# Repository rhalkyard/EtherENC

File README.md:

# ENC624J600-based Ethernet card for Acorn Archimedes and Risc PC systems

From the same person who still hasn't quite finished
[SEthernet](https://github.com/rhalkyard/SEthernet), comes yet another Ethernet
card for vintage computers!

Ethernet cards for Acorn systems are even harder to find than for vintage Macs.
This project is an attempt to bring a modern, low-cost Ethernet card to Acorn
Archimedes and Risc PC machines.

## Project Status

Early days yet! I have the driver functioning on a prototype version of the
card, but there are enough issues that it'll need a redone board before I'm
truly happy with it.

Meanwhile, someone else in the Acorn community who has access to a lot more
hardware for testing, has [announced his own open-source Ethernet
podule](https://www.stardot.org.uk/forums/viewtopic.php?p=468283). To be
brutally honest, his design is probably the sensible path forward, and there
probably isn't room for two very similar projects in such a small community, so
this project's future is in question. However, I'm proud of what I accomplished,
my design works well (in my opinion), and I think it's worth saving for
posterity, so here it is.

## Supported Systems

The intent is for this card to be compatible with any RISC OS machine with 16-
or 8-bit Podule slots, running RISC OS 3.10 or later. However, I only have
access to an A3000, so testing on later OSes and other machines will be up to
others!

## Hardware

See [HARDWARE.md](HARDWARE.md) for a design overview.

Schematic in PDF format can be found at
[pcb/EtherENC-prototype/EtherENC-Prototype.pdf](pcb/EtherENC-prototype/EtherENC-Prototype.pdf).

## Software

The [EtherENC/](EtherENC) directory contains driver source, buildable with Acorn
C/C++ version 5, which can be obtained from
[https://www.4corn.co.uk/articles/acornc5/](https://www.4corn.co.uk/articles/acornc5/),
or included in [RPCEMU](https://www.marutan.net/rpcemu/index.php)'s RISC OS 3.71
Easy-Start bundle.

If you are not used to RISC OS, the filenames and layout will look a little
weird. Instead of having extensions, `.c` and `.h` files live in separate
directories, and the comma-suffixes on various file names encode RISC OS file
types. Of particular interest, the `,ffb` files are BBC Basic programs, however
these are stored in a binary format and their source is not easily viewable on
non-RISC OS systems. Accompanying text dumps of the program code are included
alongside, I will endeavour to keep these up to date.

`MkROM` is a BASIC program that builds the card's ROM image with the appropriate
headers and loadable driver module.

`WriteROM` can then be used to program or update the card's flash with the new
ROM image.

### Checkout

Note that this repository includes the [RISC OS Open TCPIPLibs
source](https://gitlab.riscosopen.org/RiscOS/Sources/Lib/TCPIPLibs) as a
submodule. Specifically, it uses the
[TCPIPLibs-5_01](https://gitlab.riscosopen.org/RiscOS/Sources/Lib/TCPIPLibs/-/tree/TCPIPLibs-5_01)
tag, as this corresponds to the DCI 4.04 specification, without bringing in a
bunch of changes that make old versions of Acorn C/C++ get confused.

After cloning this repo, run `git submodule update --init` to set up submodules
correctly.

### Building

1. Install Acorn C/C++ and run `!SetPaths` inside the Acorn C/C++ directory.

2. Run the `!Mk` script in the source directory (or run `amu` from a TaskWindow
   or CLI).

### Flashing

1. After building the EtherENC driver, run `WriteROM` and follow the prompts.

### Installation

These instructions assume that you are using the version of `!Internet` included
in the Universal !Boot distribution. If you are using something else, you should
probably be able to figure out how to adapt them to your setup!

1. Copy `AutoSense.EtherENC` to
   `!Boot.Resources.Configure.!InetSetup.AutoSense`.

2. (optional) Copy the built `EtherENC` module to
   `!Boot.Resources.System.Modules.Network`. The driver module from the card ROM
   should be sufficient, but when testing it can be useful to softload the
   module instead.

3. Restart RISC OS.

### Configuring

Configuring the card is more or less the same as any other network interface on
RISC OS, and is done by the `!Boot.Resources.Configure.!InetSetup` application:

1. Run `!Boot.Resources.Configure.!InetSetup`, and click the `Internet` icon.

2. Under `Interfaces`, tick the box next to `EtherENC`, click the adjacent
   `Configure...` button, and set your IP address and netmask. Unless you know
   what you're doing, `Obtain IP address` should be set to `Manually`, and
   `Primary interface` should be ticked.

2. Under `Routing`, enter your default gateway. Unless you know what you're
   doing, `Act as an IP router` and `Run RouteD` should not be ticked.

3. Under `Host names`, ether your hostname domain, and DNS server(s). Ensure
   that `Use name servers also` is selected.

4. Configure AUN and Access if necessary (doing so is beyond the scope of this
   document).

#### CMOS Settings

The system's CMOS memory is used to store hardware configuration options across
reboots. These options can be set and read using RISC OS' `*Configure` and
`*Status` commands.

`*Configure EENCFlow <unit> Off|On` - Enable or disable PAUSE-frame flow
control, which may help mitigate packet drops on heavily-loaded systems. Default
is `Off`. Flow control can only operate on full-duplex links.

`*Configure EENCLink <unit> Auto | 10 Half|Full | 100 Half|Full` - Configure
link mode. `Auto` (the default) causes link speed and duplex mode to be
autonegotiated with the link partner. Otherwise, a fixed speed and duplex
setting (one of `10 Half`, `10 Full`, `100 Half` or `100 Full`) can be set.

After installing the card, or moving it into another slot, it may be necessary
to reconfigure the card in order to overwrite any leftover CMOS settings from
previous residents of that slot. Defaults can be restored with:

```
*Configure EENCLink <unit> Auto
*Configure EENCFlow <unit> Off
```

## Licenses

Hardware (everything in the `pcb` and `pld` directories) is licensed under the
CERN Open Hardware License Version 2 - Strongly Reciprocal.

The driver (everything in the `EtherENC` directory) is licensed under the GNU
Public License Version 3, with the following exceptions:

- `EtherENC.s.iocopy` contains code derived from the 
  ["Ether1" driver](https://gitlab.riscosopen.org/RiscOS/Sources/Networking/Ethernet/Ether1/) 
  as published by Risc OS Online Ltd., under the Apache License, version 2.0.

- `EtherENC.h.filter` and `EtherENC.c.filter` contain code derived from the
  ["EtherY" driver](https://gitlab.riscosopen.org/RiscOS/Sources/Networking/Ethernet/EtherY/)
  as published by RISC OS Online Ltd., under the BSD License.

- `EtherENC.h.syslog` and `EtherENC.s.syslog` are included unmodified from the
  SysLog freeware application (https://compton.nu/software/riscos/syslog).

## To Do

- Finalise hardware design

- Performance testing and driver optimisation

## Allocations

Names and IDs registered with ROOL (see
[https://www.riscosopen.org/content/allocate](https://www.riscosopen.org/content/allocate)
for info). If you fork EtherENC and make software-incompatible changes, please
request your own allocations, as these are registered to me personally. However,
if your EtherENC-derived hardware is fully compatible with the mainline EtherENC
driver, you are welcome to use the same Podule IDs.

| Allocation Type        | Allocation                                     | Source locations                                           |
| ---------------------- | ---------------------------------------------- | ---------------------------------------------------------- |
| Ethernet Driver Suffix | `ENC`                                          | Everywhere                                                 |
| SWI Base               | &5A9C0                                         | [`cmhg.ModuleHdr`](cmhg/ModuleHdr)                         |
| Module Name            | `EtherENC`                                     | [`cmhg.ModuleHdr`](cmhg/ModuleHdr)                         |
| Commands               | `EENCInfo`, `EENCTest`, `EENCFlow`, `EENCLink` | [`cmhg.ModuleHdr`](cmhg/ModuleHdr), [`c.module`](c/module) |
| Error Block            | &822800                                        | [`h.errors`](h/errors), [`MkROM`](MkROM.bas)               |
| Podule Manufacturer ID | &72                                            | [`h.if_enc`](h/if_enc), [`MkROM`](MkROM.bas)               |
| Podule Type ID         | &14E (16 bit), &14F (8 bit)                    | [`h.if_enc`](h/if_enc), [`MkROM`](MkROM.bas)               |

## References

- [RISC OS 3 Programmer's Reference Manual](http://www.riscos.com/support/developers/prm/)

- [Acorn Enhanced Expansion Card
  Specification](https://www.chiark.greenend.org.uk/~theom/riscos/docs/expspec.pdf)

- [RISC OS DCI4 Reference Manuals](https://gerph.github.io/riscos-prm-dci4/)

- [Ether1 (AMD LANCE-based card) driver source](https://gitlab.riscosopen.org/RiscOS/Sources/Networking/Ethernet/Ether1)

- [EtherY (LAN91C111-based card) driver source](https://gitlab.riscosopen.org/RiscOS/Sources/Networking/Ethernet/EtherY/)

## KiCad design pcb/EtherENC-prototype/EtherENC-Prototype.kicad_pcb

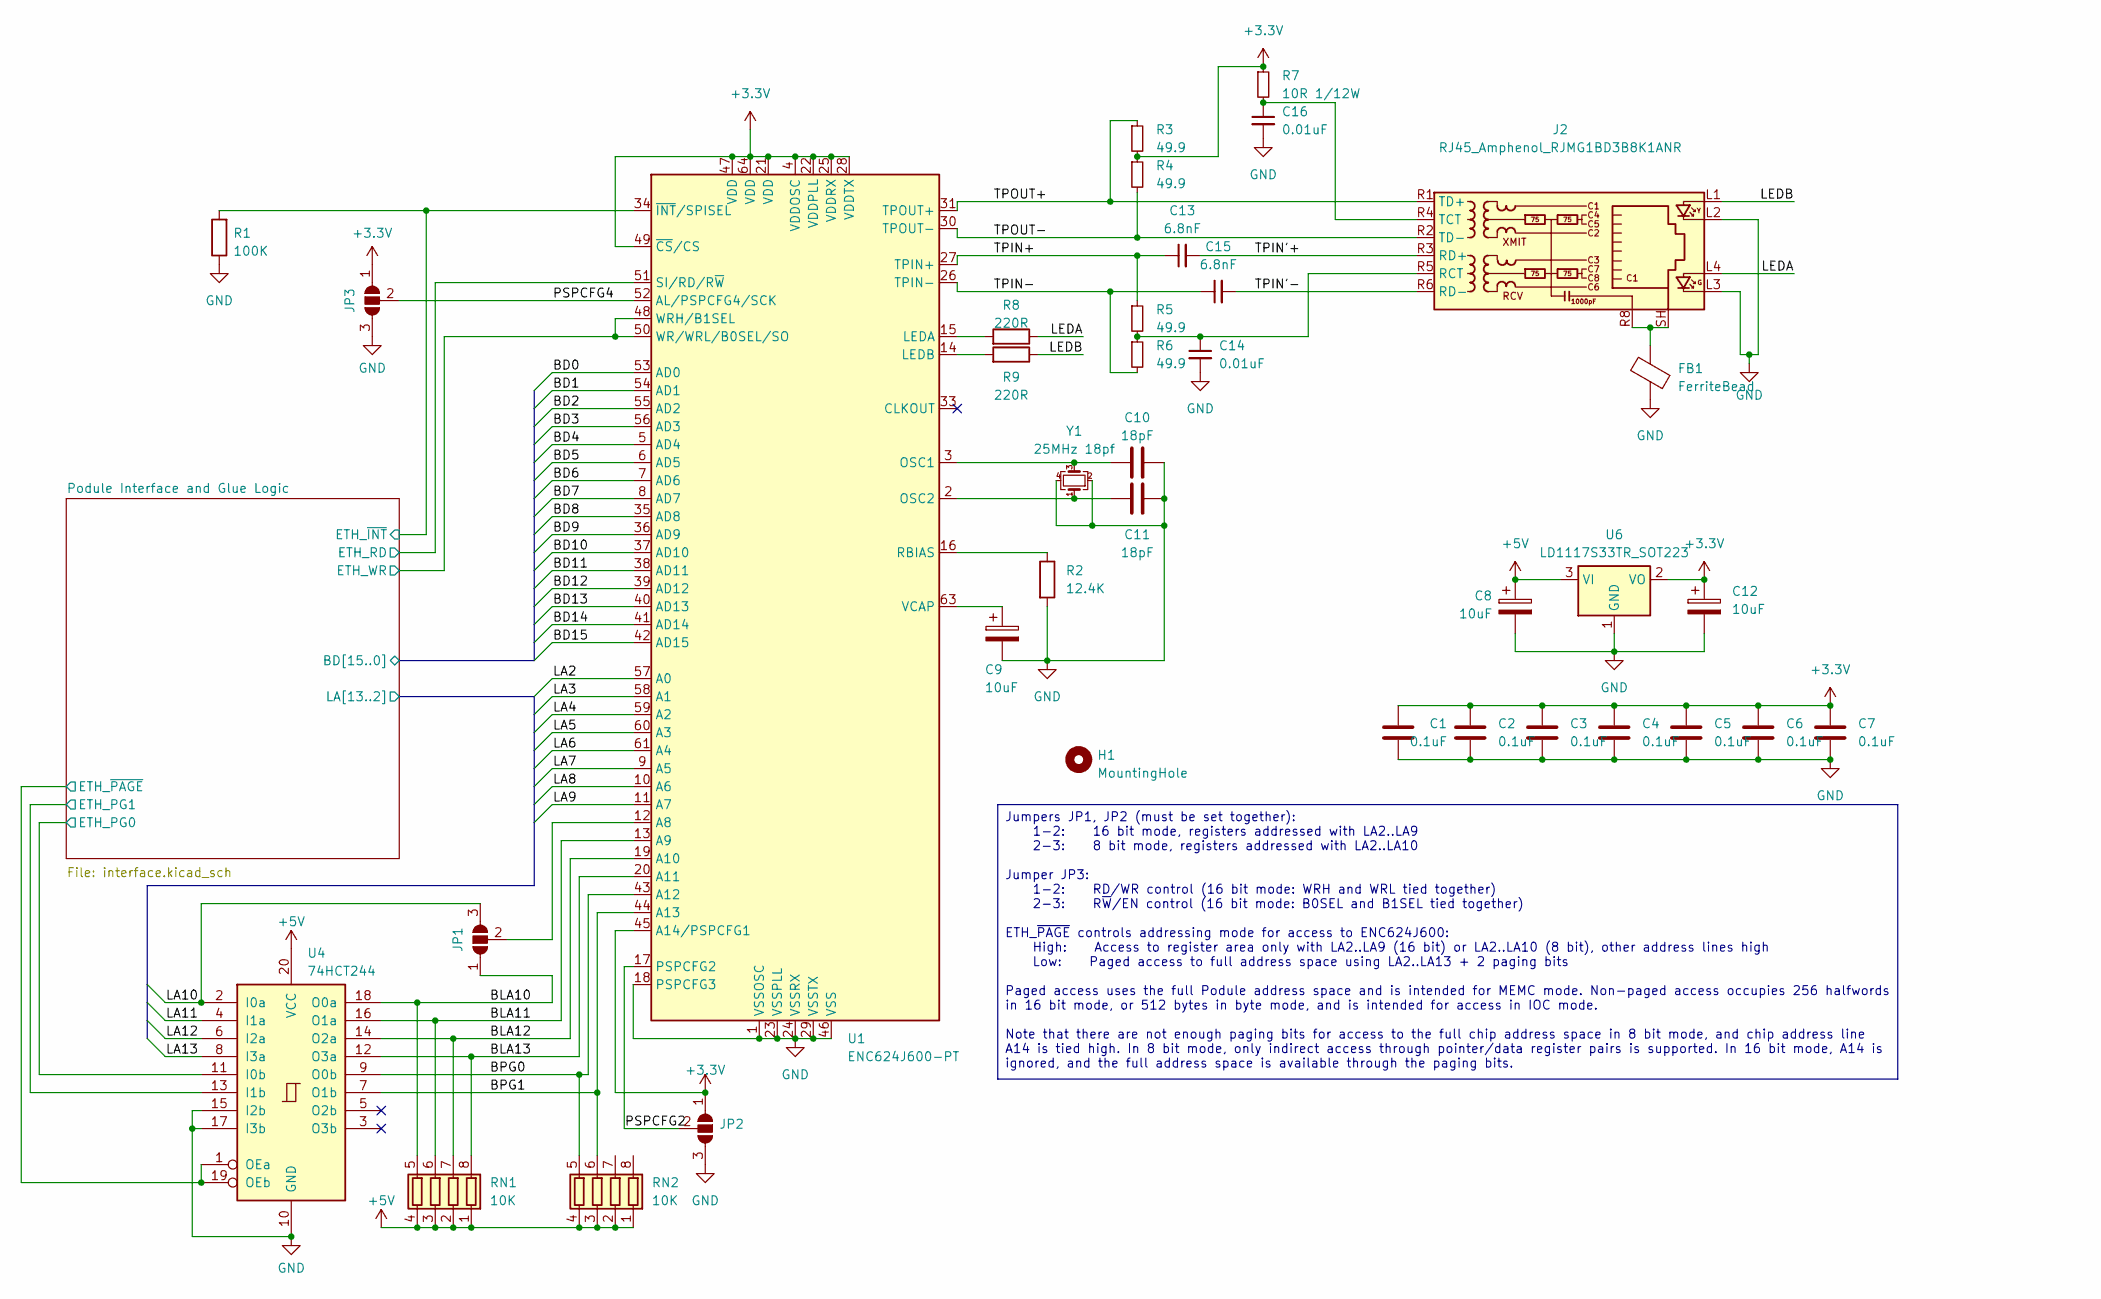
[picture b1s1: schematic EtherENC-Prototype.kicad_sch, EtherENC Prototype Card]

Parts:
C1, C2, C3, C4, C5, C6, C7: 0.1uF; C_0805_2012Metric_Pad1.18x1.45mm_HandSolder; Digikey 399-C0805C104M5RAC7800CT-ND
C8, C9, C12: 10uF; CP_EIA-3216-18_Kemet-A_Pad1.58x1.35mm_HandSolder; Digikey 718-1118-1-ND
C10, C11: 18pF; C_0805_2012Metric_Pad1.18x1.45mm_HandSolder; Digikey 399-C0805C180K5GAC7800CT-ND
C13, C15: 6.8nF; C_0805_2012Metric_Pad1.18x1.45mm_HandSolder; Digikey 399-C0805C682K5RAC7800CT-ND
C14, C16: 0.01uF; C_0805_2012Metric_Pad1.18x1.45mm_HandSolder; Digikey 399-C0805C103K5RACTUCT-ND
FB1: FerriteBead; L_0805_2012Metric_Pad1.15x1.40mm_HandSolder; Digikey 240-2549-1-ND
H1: MountingHole; MountingHole_3.2mm_M3
J2: RJ45_Amphenol_RJMG1BD3B8K1ANR; Digikey RJMG1BD3B8K1ANR-ND
JP1, JP2, JP3: SolderJumper_3_Open; SolderJumper-3_P1.3mm_Open_RoundedPad1.0x1.5mm
R1: 100K; R_0805_2012Metric_Pad1.20x1.40mm_HandSolder; Digikey RMCF0805FT100KCT-ND
R2: 12.4K; R_0805_2012Metric_Pad1.20x1.40mm_HandSolder; Digikey RMCF0805FT12K4CT-ND
R3, R4, R5, R6: 49.9; R_0805_2012Metric_Pad1.20x1.40mm_HandSolder; Digikey RMCF0805FT49R9CT-ND
R7: 10R 1/12W; R_0805_2012Metric_Pad1.20x1.40mm_HandSolder; Digikey RMCF0805FT10R0CT-ND
R8, R9: 220R; R_0805_2012Metric_Pad1.20x1.40mm_HandSolder; Digikey RMCF0805FT221RCT-ND
RN1, RN2: 10K; R_Array_Concave_4x0603; Digikey CAT16-103J4LFCT-ND
U1: ENC624J600-PT; TQFP-64_10x10mm_P0.5mm; Digikey ENC624J600-I/PT-ND
U4: 74HCT244; TSSOP-20_4.4x6.5mm_P0.65mm; Digikey 296-8402-1-ND
U6: LD1117S33TR_SOT223; SOT-223-3_TabPin2; Digikey 497-1242-1-ND
Y1: 25MHz 18pf; Crystal_SMD_3225-4Pin_3.2x2.5mm_HandSoldering; Digikey 2151-RH100-25.000-18-F-1020-EXT-TRCT-ND

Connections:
+3.3V: C1.2, C2.1, C3.1, C4.2, C5.1, C6.2, C7.1, C12.1, JP2.1 (A), JP3.1 (A), R3.2, R4.1, R7.1, U1.4 (VDDOSC), U1.21 (VDD), U1.22 (VDDPLL), U1.25 (VDDRX), U1.28 (VDDTX), U1.45 (A14/PSPCFG1), U1.47 (VDD), U1.49 (~CS/CS), U1.64 (VDD), U6.2 (VO)
+5V: C8.1, RN1.1 (R1.1), RN1.2 (R2.1), RN1.3 (R3.1), RN1.4 (R4.1), RN2.1 (R1.1), RN2.2 (R2.1), RN2.3 (R3.1), RN2.4 (R4.1), U4.20 (VCC), U6.3 (VI); also elsewhere on the board
/BLA10: JP1.1 (A), RN1.5 (R4.2), U4.18 (O0a)
/BLA11: RN1.6 (R3.2), U1.13 (A9), U4.16 (O1a)
/BLA12: RN1.7 (R2.2), U1.19 (A10), U4.14 (O2a)
/BLA13: RN1.8 (R1.2), U1.20 (A11), U4.12 (O3a)
/BPG0: RN2.5 (R4.2), U1.43 (A12), U4.9 (O0b)
/BPG1: RN2.6 (R3.2), U1.44 (A13), U4.7 (O1b)
/LEDA: J2.L4, R8.1
/LEDB: J2.L1, R9.1
/PSPCFG2: JP2.2 (C), U1.17 (PSPCFG2)
/PSPCFG4: JP3.2 (C), U1.52 (AL/PSPCFG4/SCK)
/Podule Interface and Glue Logic/BD0: U1.53 (AD0); also elsewhere on the board
/Podule Interface and Glue Logic/BD1: U1.54 (AD1); also elsewhere on the board
/Podule Interface and Glue Logic/BD2: U1.55 (AD2); also elsewhere on the board
/Podule Interface and Glue Logic/BD3: U1.56 (AD3); also elsewhere on the board
/Podule Interface and Glue Logic/BD4: U1.5 (AD4); also elsewhere on the board
/Podule Interface and Glue Logic/BD5: U1.6 (AD5); also elsewhere on the board
/Podule Interface and Glue Logic/BD6: U1.7 (AD6); also elsewhere on the board
/Podule Interface and Glue Logic/BD7: U1.8 (AD7); also elsewhere on the board
/Podule Interface and Glue Logic/BD8: U1.35 (AD8); also elsewhere on the board
/Podule Interface and Glue Logic/BD9: U1.36 (AD9); also elsewhere on the board
/Podule Interface and Glue Logic/BD10: U1.37 (AD10); also elsewhere on the board
/Podule Interface and Glue Logic/BD11: U1.38 (AD11); also elsewhere on the board
/Podule Interface and Glue Logic/BD12: U1.39 (AD12); also elsewhere on the board
/Podule Interface and Glue Logic/BD13: U1.40 (AD13); also elsewhere on the board
/Podule Interface and Glue Logic/BD14: U1.41 (AD14); also elsewhere on the board
/Podule Interface and Glue Logic/BD15: U1.42 (AD15); also elsewhere on the board
/Podule Interface and Glue Logic/ETH_PG0: U4.11 (I0b); also elsewhere on the board
/Podule Interface and Glue Logic/ETH_PG1: U4.13 (I1b); also elsewhere on the board
/Podule Interface and Glue Logic/ETH_RD: U1.51 (SI/RD/R~W); also elsewhere on the board
/Podule Interface and Glue Logic/ETH_WR: U1.48 (WRH/B1SEL), U1.50 (WR/WRL/B0SEL/SO); also elsewhere on the board
/Podule Interface and Glue Logic/ETH_~INT: R1.2, U1.34 (~INT/SPISEL); also elsewhere on the board
/Podule Interface and Glue Logic/ETH_~PAGE: U4.1 (OEa), U4.19 (OEb); also elsewhere on the board
/Podule Interface and Glue Logic/LA2: U1.57 (A0); also elsewhere on the board
/Podule Interface and Glue Logic/LA3: U1.58 (A1); also elsewhere on the board
/Podule Interface and Glue Logic/LA4: U1.59 (A2); also elsewhere on the board
/Podule Interface and Glue Logic/LA5: U1.60 (A3); also elsewhere on the board
/Podule Interface and Glue Logic/LA6: U1.61 (A4); also elsewhere on the board
/Podule Interface and Glue Logic/LA7: U1.9 (A5); also elsewhere on the board
/Podule Interface and Glue Logic/LA8: U1.10 (A6); also elsewhere on the board
/Podule Interface and Glue Logic/LA9: U1.11 (A7); also elsewhere on the board
/Podule Interface and Glue Logic/LA10: JP1.3 (B), U4.2 (I0a); also elsewhere on the board
/Podule Interface and Glue Logic/LA11: U4.4 (I1a); also elsewhere on the board
/Podule Interface and Glue Logic/LA12: U4.6 (I2a); also elsewhere on the board
/Podule Interface and Glue Logic/LA13: U4.8 (I3a); also elsewhere on the board
/TPIN'+: C13.2, J2.R3 (RD+)
/TPIN'-: C15.2, J2.R6 (RD-)
/TPIN+: C13.1, R5.1, U1.27 (TPIN+)
/TPIN-: C15.1, R6.2, U1.26 (TPIN-)
/TPOUT+: J2.R1 (TD+), R3.1, U1.31 (TPOUT+)
/TPOUT-: J2.R2 (TD-), R4.2, U1.30 (TPOUT-)
GND: C1.1, C2.2, C3.2, C4.1, C5.2, C6.1, C7.2, C8.2, C9.2, C10.2, C11.2, C12.2, C14.2, C16.2, FB1.1, J2.L2, J2.L3, JP2.3 (B), JP3.3 (B), R1.1, R2.2, U1.1 (VSSOSC), U1.18 (PSPCFG3), U1.23 (VSSPLL), U1.24 (VSSRX), U1.29 (VSSTX), U1.32 (VSSTX), U1.46 (VSS), U1.62 (VSS), U4.10 (GND), U4.15 (I2b), U4.17 (I3b), U6.1 (GND), Y1.2, Y1.4; also elsewhere on the board
unnamed: FB1.2, J2.R8, J2.SH
unnamed: C14.1, J2.R5 (RCT), R5.2, R6.1
unnamed: C16.1, J2.R4 (TCT), R7.2
unnamed: JP1.2 (C), U1.12 (A8)
unnamed: R8.2, U1.15 (LEDA)
unnamed: R9.2, U1.14 (LEDB)
unnamed: C10.1, U1.3 (OSC1), Y1.3
unnamed: C11.1, U1.2 (OSC2), Y1.1
unnamed: R2.1, U1.16 (RBIAS)
unnamed: C9.1, U1.63 (VCAP)

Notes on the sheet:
Jumpers JP1, JP2 (must be set together): 1-2: 16 bit mode, registers addressed with LA2..LA9 2-3: 8 bit mode, registers addressed with LA2..LA10 Jumper JP3: 1-2: RD/WR control (16 bit mode: WRH and WRL tied together) 2-3: R~{W}/EN control (16 bit mode: B0SEL and B1SEL tied together) ETH_~{PAGE} con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

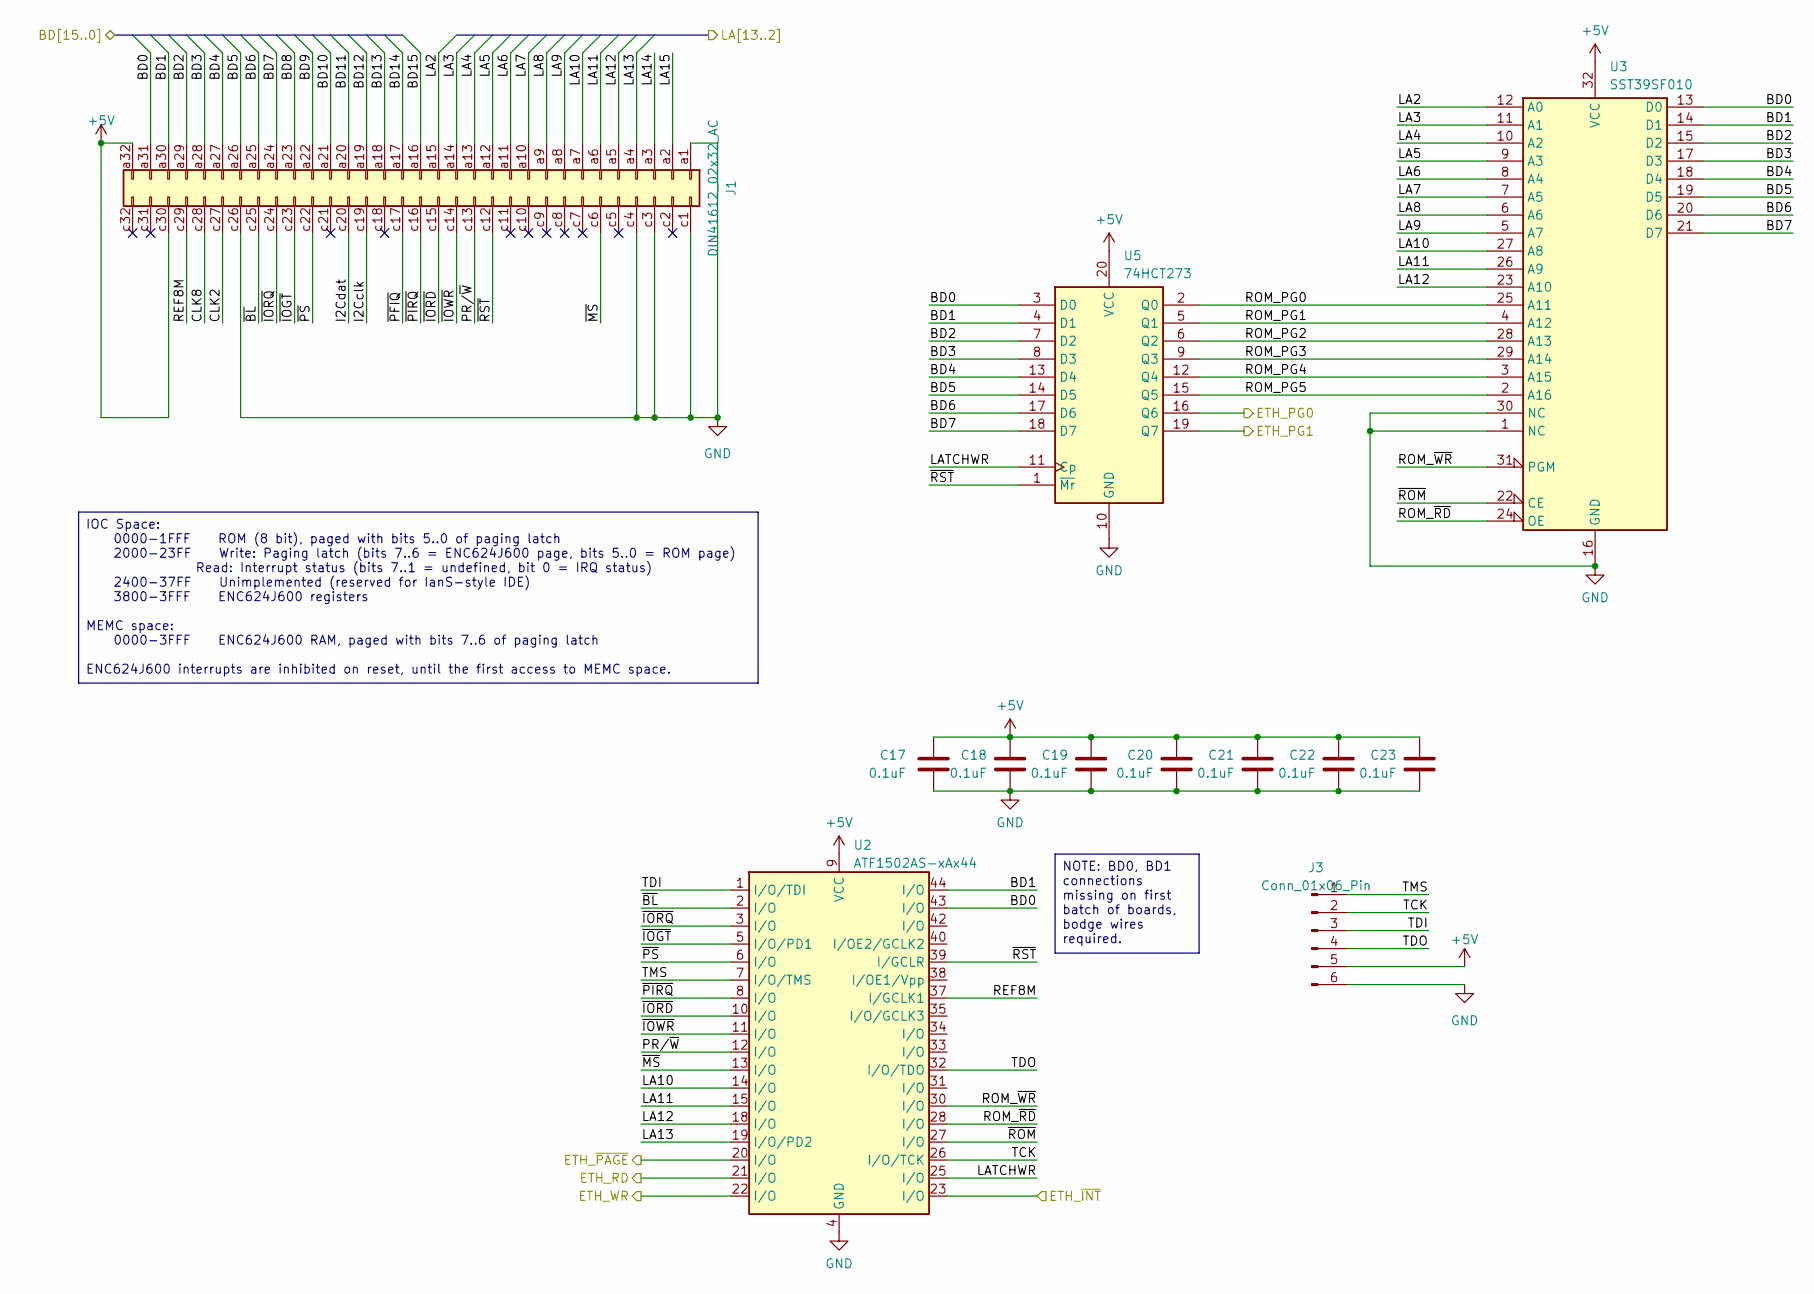
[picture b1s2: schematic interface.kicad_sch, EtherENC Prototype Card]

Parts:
C17, C18, C19, C20, C21, C22, C23: 0.1uF; C_0805_2012Metric_Pad1.18x1.45mm_HandSolder; Digikey 399-C0805C104M5RAC7800CT-ND
J1: DIN41612_02x32_AC; DIN41612_C_3x32_Male_Horizontal_THT
J3: Conn_01x06_Pin; PinHeader_1x06_P2.54mm_Vertical
U2: ATF1502AS-xAx44; TQFP-44_10x10mm_P0.8mm; Digikey ATF1502AS-10AU44-ND
U3: SST39SF010; PLCC-32_THT-Socket; Digikey SST39SF010A-70-4C-NHE-ND
U5: 74HCT273; TSSOP-20_4.4x6.5mm_P0.65mm; Digikey 296-8409-1-ND

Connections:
+5V: C17.2, C18.2, C19.2, C20.2, C21.2, C22.2, C23.2, J1.a32, J1.c30, J3.5, U2.9 (VCC), U2.17 (VCC), U2.29 (VCC), U2.41 (VCC), U3.32 (VCC), U5.20 (VCC); also elsewhere on the board
/Podule Interface and Glue Logic/BD0: J1.a31, U2.43 (I/O), U3.13 (D0), U5.3 (D0); also elsewhere on the board
/Podule Interface and Glue Logic/BD1: J1.a30, U2.44 (I/O), U3.14 (D1), U5.4 (D1); also elsewhere on the board
/Podule Interface and Glue Logic/BD2: J1.a29, U3.15 (D2), U5.7 (D2); also elsewhere on the board
/Podule Interface and Glue Logic/BD3: J1.a28, U3.17 (D3), U5.8 (D3); also elsewhere on the board
/Podule Interface and Glue Logic/BD4: J1.a27, U3.18 (D4), U5.13 (D4); also elsewhere on the board
/Podule Interface and Glue Logic/BD5: J1.a26, U3.19 (D5), U5.14 (D5); also elsewhere on the board
/Podule Interface and Glue Logic/BD6: J1.a25, U3.20 (D6), U5.17 (D6); also elsewhere on the board
/Podule Interface and Glue Logic/BD7: J1.a24, U3.21 (D7), U5.18 (D7); also elsewhere on the board
/Podule Interface and Glue Logic/BD8: J1.a23; also elsewhere on the board
/Podule Interface and Glue Logic/BD9: J1.a22; also elsewhere on the board
/Podule Interface and Glue Logic/BD10: J1.a21; also elsewhere on the board
/Podule Interface and Glue Logic/BD11: J1.a20; also elsewhere on the board
/Podule Interface and Glue Logic/BD12: J1.a19; also elsewhere on the board
/Podule Interface and Glue Logic/BD13: J1.a18; also elsewhere on the board
/Podule Interface and Glue Logic/BD14: J1.a17; also elsewhere on the board
/Podule Interface and Glue Logic/BD15: J1.a16; also elsewhere on the board
/Podule Interface and Glue Logic/CLK2: J1.c27
/Podule Interface and Glue Logic/CLK8: J1.c28
/Podule Interface and Glue Logic/ETH_PG0: U5.16 (Q6); also elsewhere on the board
/Podule Interface and Glue Logic/ETH_PG1: U5.19 (Q7); also elsewhere on the board
/Podule Interface and Glue Logic/ETH_RD: U2.21 (I/O); also elsewhere on the board
/Podule Interface and Glue Logic/ETH_WR: U2.22 (I/O); also elsewhere on the board
/Podule Interface and Glue Logic/ETH_~INT: U2.23 (I/O); also elsewhere on the board
/Podule Interface and Glue Logic/ETH_~PAGE: U2.20 (I/O); also elsewhere on the board
/Podule Interface and Glue Logic/I2Cclk: J1.c19
/Podule Interface and Glue Logic/I2Cdat: J1.c20
/Podule Interface and Glue Logic/LA2: J1.a15, U3.12 (A0); also elsewhere on the board
/Podule Interface and Glue Logic/LA3: J1.a14, U3.11 (A1); also elsewhere on the board
/Podule Interface and Glue Logic/LA4: J1.a13, U3.10 (A2); also elsewhere on the board
/Podule Interface and Glue Logic/LA5: J1.a12, U3.9 (A3); also elsewhere on the board
/Podule Interface and Glue Logic/LA6: J1.a11, U3.8 (A4); also elsewhere on the board
/Podule Interface and Glue Logic/LA7: J1.a10, U3.7 (A5); also elsewhere on the board
/Podule Interface and Glue Logic/LA8: J1.a9, U3.6 (A6); also elsewhere on the board
/Podule Interface and Glue Logic/LA9: J1.a8, U3.5 (A7); also elsewhere on the board
/Podule Interface and Glue Logic/LA10: J1.a7, U2.14 (I/O), U3.27 (A8); also elsewhere on the board
/Podule Interface and Glue Logic/LA11: J1.a6, U2.15 (I/O), U3.26 (A9); also elsewhere on the board
/Podule Interface and Glue Logic/LA12: J1.a5, U2.18 (I/O), U3.23 (A10); also elsewhere on the board
/Podule Interface and Glue Logic/LA13: J1.a4, U2.19 (I/O/PD2); also elsewhere on the board
/Podule Interface and Glue Logic/LA14: J1.a3
/Podule Interface and Glue Logic/LA15: J1.a2
/Podule Interface and Glue Logic/LATCHWR: U2.25 (I/O), U5.11 (Cp)
/Podule Interface and Glue Logic/PR/~W: J1.c13, U2.12 (I/O)
/Podule Interface and Glue Logic/REF8M: J1.c29, U2.37 (I/GCLK1)
/Podule Interface and Glue Logic/ROM_PG0: U3.25 (A11), U5.2 (Q0)
/Podule Interface and Glue Logic/ROM_PG1: U3.4 (A12), U5.5 (Q1)
/Podule Interface and Glue Logic/ROM_PG2: U3.28 (A13), U5.6 (Q2)
/Podule Interface and Glue Logic/ROM_PG3: U3.29 (A14), U5.9 (Q3)
/Podule Interface and Glue Logic/ROM_PG4: U3.3 (A15), U5.12 (Q4)
/Podule Interface and Glue Logic/ROM_PG5: U3.2 (A16), U5.15 (Q5)
/Podule Interface and Glue Logic/ROM_~RD: U2.28 (I/O), U3.24 (OE)
/Podule Interface and Glue Logic/ROM_~WR: U2.30 (I/O), U3.31 (PGM)
/Podule Interface and Glue Logic/TCK: J3.2, U2.26 (I/O/TCK)
/Podule Interface and Glue Logic/TDI: J3.3, U2.1 (I/O/TDI)
/Podule Interface and Glue Logic/TDO: J3.4, U2.32 (I/O/TDO)
/Podule Interface and Glue Logic/TMS: J3.1, U2.7 (I/O/TMS)
/Podule Interface and Glue Logic/~BL: J1.c25, U2.2 (I/O)
/Podule Interface and Glue Logic/~IOGT: J1.c23, U2.5 (I/O/PD1)
/Podule Interface and Glue Logic/~IORD: J1.c15, U2.10 (I/O)
/Podule Interface and Glue Logic/~IORQ: J1.c24, U2.3 (I/O)
/Podule Interface and Glue Logic/~IOWR: J1.c14, U2.11 (I/O)
/Podule Interface and Glue Logic/~MS: J1.c6, U2.13 (I/O)
/Podule Interface and Glue Logic/~PFIQ: J1.c17
/Podule Interface and Glue Logic/~PIRQ: J1.c16, U2.8 (I/O)
/Podule Interface and Glue Logic/~PS: J1.c22, U2.6 (I/O)
/Podule Interface and Glue Logic/~ROM: U2.27 (I/O), U3.22 (CE)
/Podule Interface and Glue Logic/~RST: J1.c12, U2.39 (I/GCLR), U5.1 (~Mr)
GND: C17.1, C18.1, C19.1, C20.1, C21.1, C22.1, C23.1, J1.a1, J1.c1, J1.c3, J1.c4, J1.c26, J3.6, U2.4 (GND), U2.16 (GND), U2.24 (GND), U2.36 (GND), U3.1 (NC), U3.16 (GND), U3.30 (NC), U5.10 (GND); also elsewhere on the board

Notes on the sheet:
NOTE: BD0, BD1 connections missing on first batch of boards, bodge wires required.
IOC Space: 0000-1FFF ROM (8 bit), paged with bits 5..0 of paging latch 2000-23FF Write: Paging latch (bits 7..6 = ENC624J600 page, bits 5..0 = ROM page) Read: Interrupt status (bits 7..1 = undefined, bit 0 = IRQ status) 2400-37FF Unimplemented (reserved for IanS-style IDE) 3800-3FFF ENC624J600 regi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

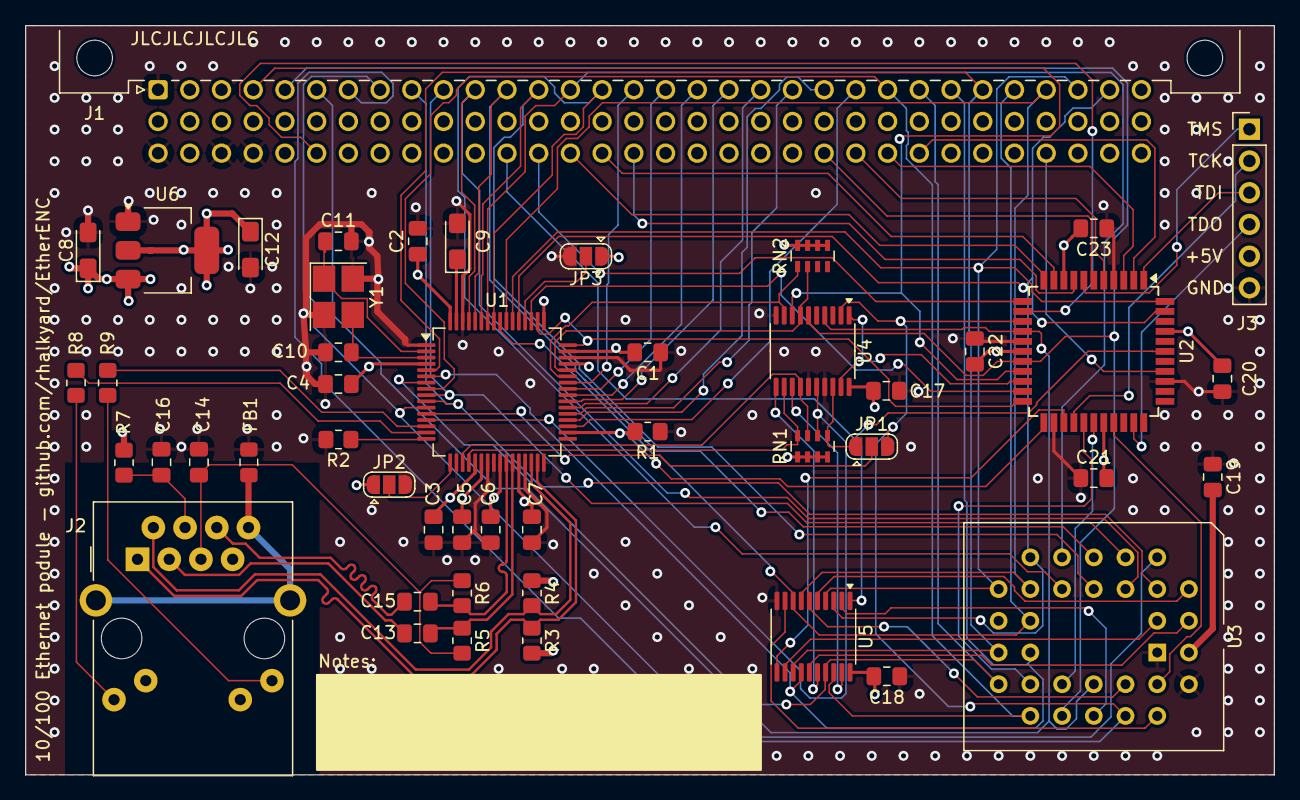
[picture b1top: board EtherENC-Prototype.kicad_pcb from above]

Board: 4 copper layers, 100.0 x 60.0 mm, 49 parts (0 on the bottom side), 88 nets.

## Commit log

2025-10-28 Add text-format versions of BASIC progs
2025-10-28 Add note on project status and future
2025-10-28 Fix broken link
2025-10-30 Make hardware description match current hardware
2025-10-30 Fix debug-macro names
2025-11-01 PLD logic revisions
    Previous version more-or-less worked but violated timings. This version
    ought to be militantly correct.
2025-11-01 Unmask IRQs when possible
2025-11-02 Tidy up command defs
2025-11-02 Improved diags and attempt at RX error handling
2025-11-03 Migrate TCPIPLibs to submodule
2025-11-10 Avoid catch 22 when writing flash to blank part - when Podule_HardwareAddresses won't work because there's no active podule yet
2025-11-24 log more detail for TX and RX errors
2025-11-24 Hold chip-registers pointer as register var
    The Norcroft compiler seems reluctant to maintain registers for things
    like `ctx->regs`, no matter how frequently they get accessed. Forcibly
    cache it in a register variable where it makes sense; this noticeably
    reduces code size at the cost of maybe 1 register spill.
2025-11-24 correct stats reporting of link status and polarity
2025-11-24 Set high bit of LA debug words to indicate error
2025-11-24 Use proper ROOL-allocated IDs
    Change *-command prefix to `EENC` (vs `ENC`) per request from ROOL.
    Correct error numbers returned by ROM loader
2025-11-24 Correct licensing for ROOL-derived bits. Sorry!
2025-11-24 Get rid of cmhg preprocessor tricks
    Older versions of cmhg don't support preprocessing
2025-11-24 gitattributes for weird acorn files
2025-11-24 fix mbuf leak when transmitting multiple chains
2025-11-24 Simplify debug logging
    Logging of transmits, receives, and IRQ entry/exit is no longer really
    needed, and its presence made the code less readable. Get rid of it.
2025-11-24 Finish missing sentence about ID allocations
2025-11-24 fix line endings
